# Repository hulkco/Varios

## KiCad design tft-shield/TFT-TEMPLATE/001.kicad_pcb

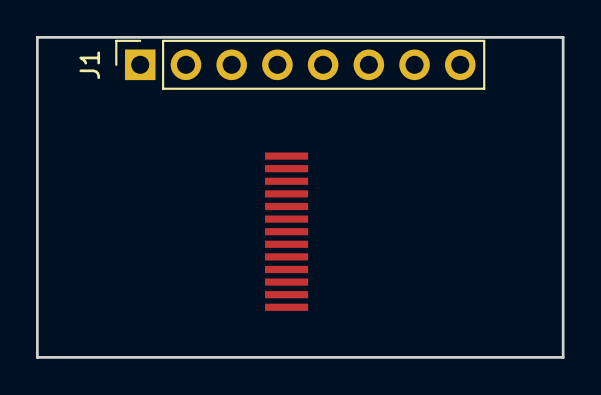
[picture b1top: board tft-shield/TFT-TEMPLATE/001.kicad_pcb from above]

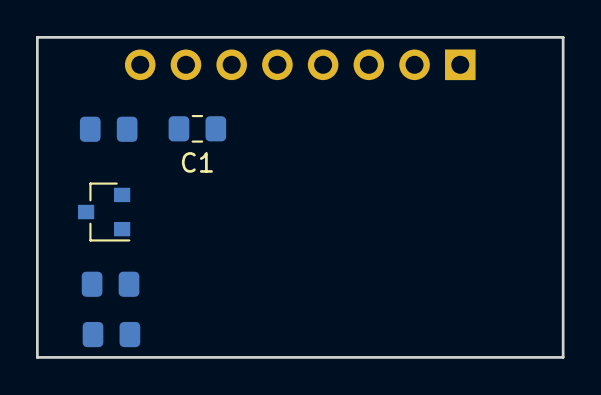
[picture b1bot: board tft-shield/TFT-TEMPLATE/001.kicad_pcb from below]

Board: 2 copper layers, 29.2 x 17.8 mm, 7 parts (5 on the bottom side), 12 nets, no tracks yet.

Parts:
C1: 1uF; C_0805_2012Metric_Pad1.15x1.40mm_HandSolder
J1: CONN_01X08; PinSocket_1x08_P2.54mm_Vertical
Q1: S8050; SOT-23
R1: 1k; R_0805_2012Metric_Pad1.15x1.40mm_HandSolder
R2: 10k; R_0805_2012Metric_Pad1.15x1.40mm_HandSolder
R3: 10ohm; R_0805_2012Metric_Pad1.15x1.40mm_HandSolder
U1: TFT_0.9680*160; TFT_0.96_SPI

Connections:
/BLK: J1.3, R1.2
/CS: J1.4, U1.7
/DC: J1.6, U1.5
/LEDK: R3.1, U1.11
/RES: J1.5, U1.6
/SCL: J1.7, U1.4
/SDA: J1.8, U1.3
GND: C1.2, J1.1, Q1.1, U1.8, U1.13
unnamed: C1.1, U1.10
unnamed: Q1.2, R1.1, R2.1
unnamed: Q1.3, R3.2
VCC: J1.2, R2.2, U1.12

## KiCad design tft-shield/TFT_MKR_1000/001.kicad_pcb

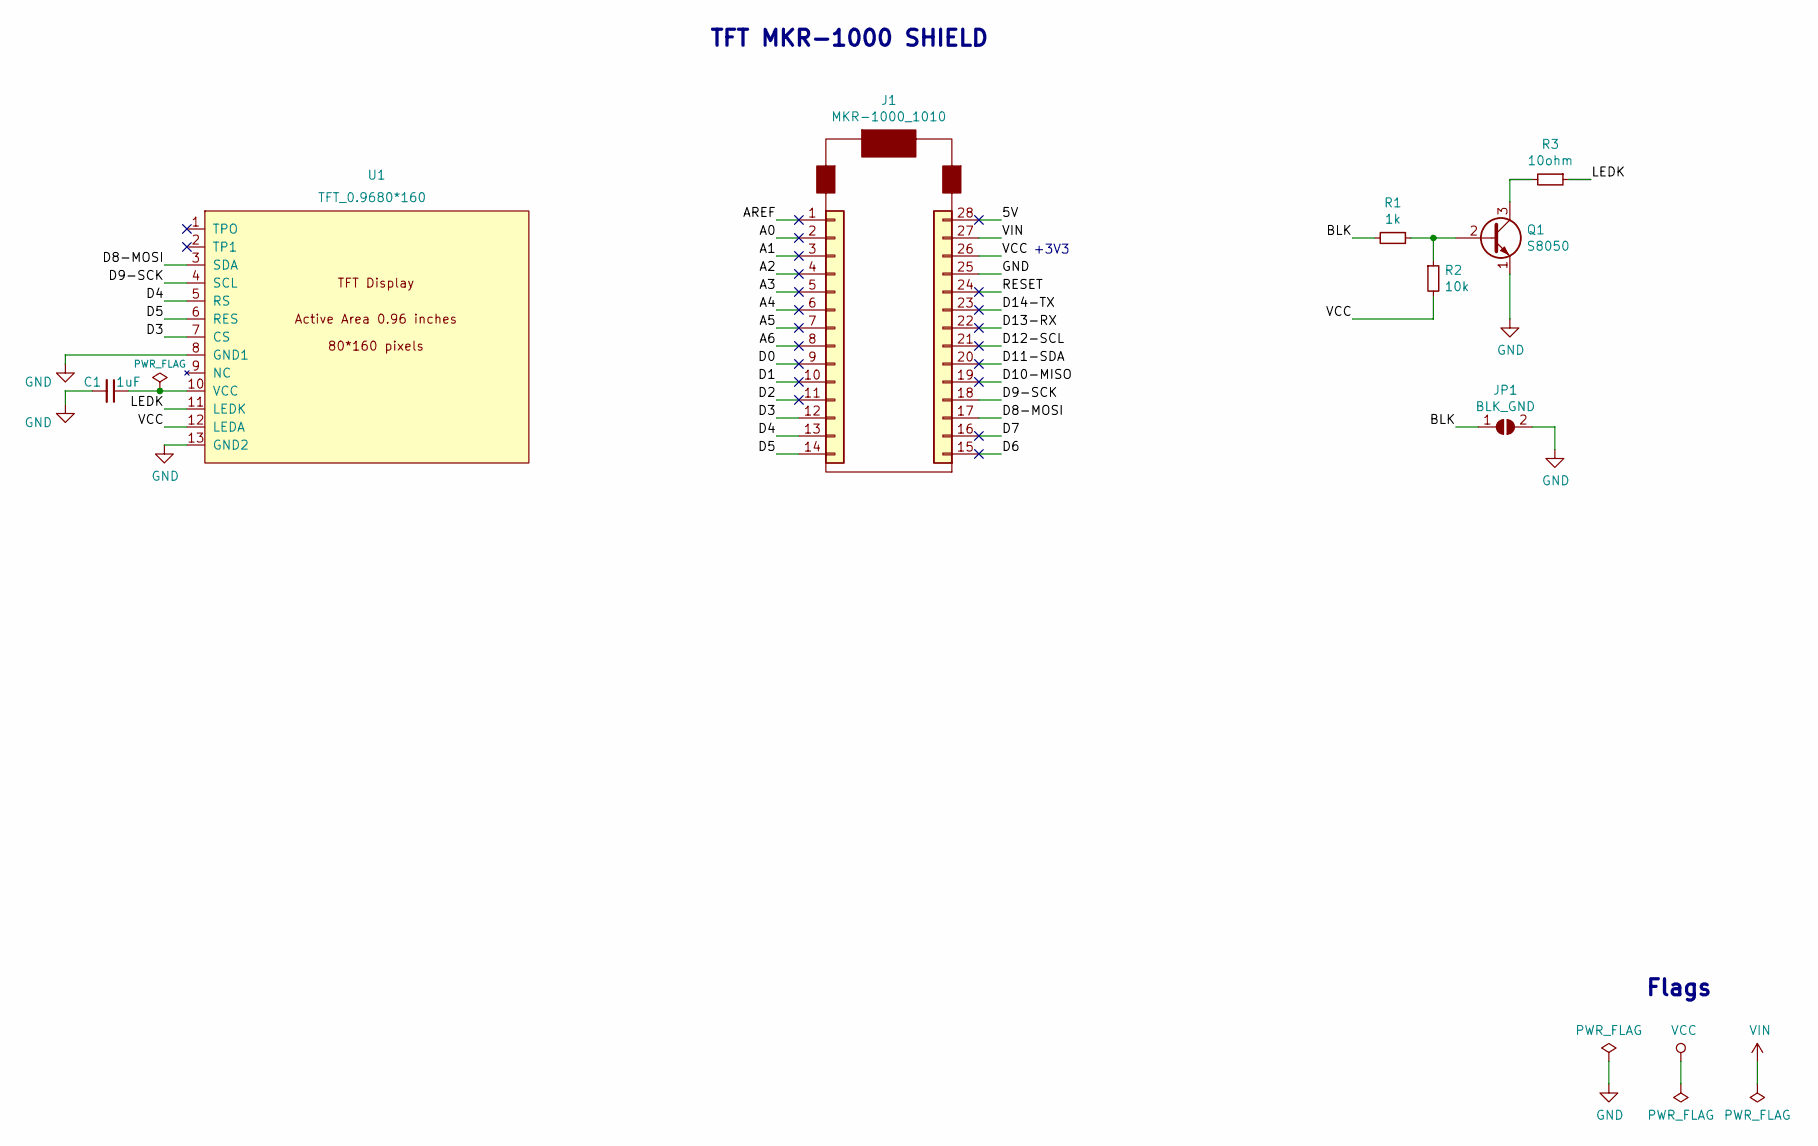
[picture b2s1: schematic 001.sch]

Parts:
C1: 1uF; C_0805_2012Metric_Pad1.15x1.40mm_HandSolder
J1: MKR-1000_1010; MKR-1000-1010
JP1: BLK_GND; SolderJumper-2_P1.3mm_Open_RoundedPad1.0x1.5mm
Q1: S8050; SOT-23
R1: 1k; R_0805_2012Metric_Pad1.15x1.40mm_HandSolder
R2: 10k; R_0805_2012Metric_Pad1.15x1.40mm_HandSolder
R3: 10ohm; R_0805_2012Metric_Pad1.15x1.40mm_HandSolder
U1: TFT_0.9680*160; TFT_0.96_SPI

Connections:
/5V: J1.28
/A0: J1.2
/A1: J1.3
/A2: J1.4
/A3: J1.5
/A4: J1.6
/A5: J1.7
/A6: J1.8
/AREF: J1.1
/BLK: JP1.1 (A), R1.2
/D0: J1.9
/D1: J1.10
/D2: J1.11
/D3: J1.12, U1.7 (CS)
/D4: J1.13, U1.5 (RS)
/D5: J1.14, U1.6 (RES)
/D6: J1.15
/D7: J1.16
/D8-MOSI: J1.17, U1.3 (SDA)
/D9-SCK: J1.18, U1.4 (SCL)
/D10-MISO: J1.19
/D11-SDA: J1.20
/D12-SCL: J1.21
/D13-RX: J1.22
/D14-TX: J1.23
/LEDK: R3.1, U1.11 (LEDK)
/RESET: J1.24
GND: C1.2, J1.25, JP1.2 (B), Q1.1 (E), U1.8 (GND1), U1.13 (GND2)
unnamed: C1.1, U1.10 (VCC)
unnamed: Q1.2 (B), R1.1, R2.1
unnamed: Q1.3 (C), R3.2
VCC: J1.26, R2.2, U1.12 (LEDA)
VIN: J1.27

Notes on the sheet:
TFT MKR-1000 SHIELD
Flags
+3V3

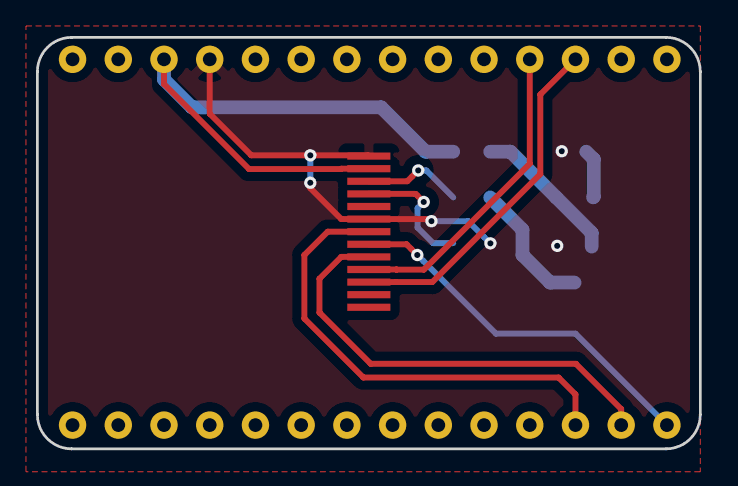
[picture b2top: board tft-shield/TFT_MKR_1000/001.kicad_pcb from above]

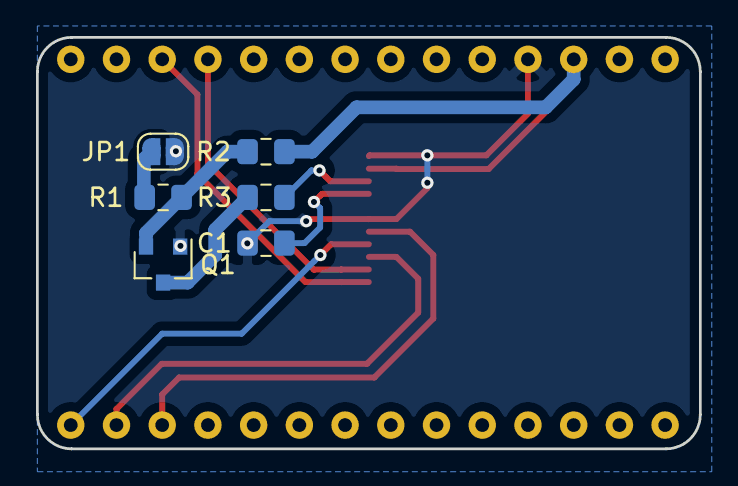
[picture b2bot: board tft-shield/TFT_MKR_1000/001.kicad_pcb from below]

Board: 2 copper layers, 36.8 x 22.9 mm, 8 parts (6 on the bottom side), 12 nets.

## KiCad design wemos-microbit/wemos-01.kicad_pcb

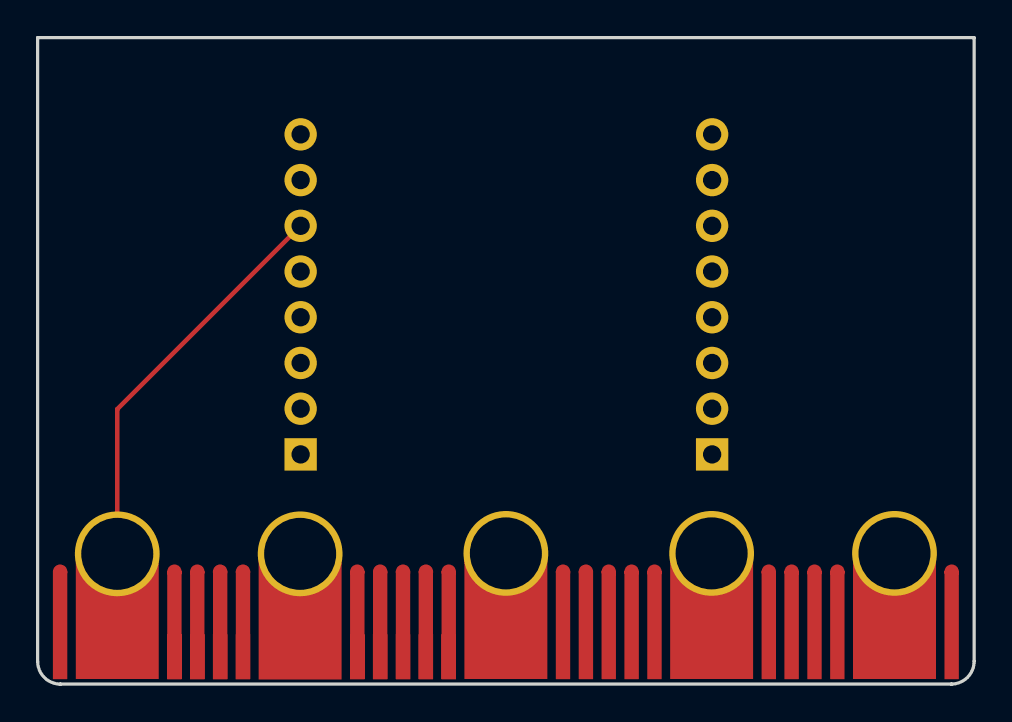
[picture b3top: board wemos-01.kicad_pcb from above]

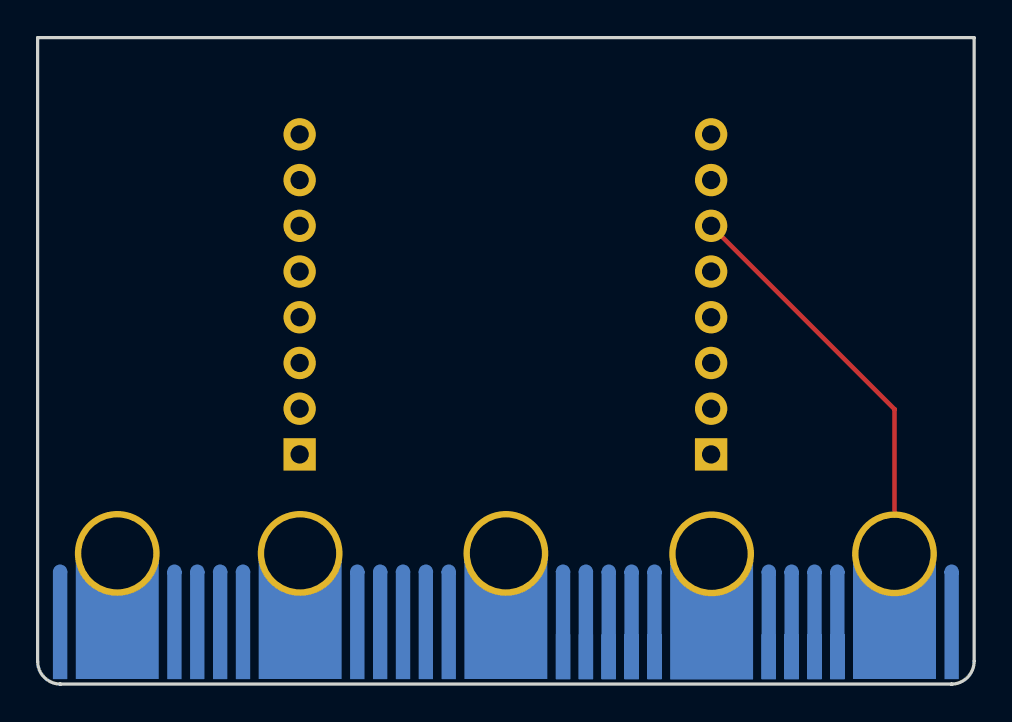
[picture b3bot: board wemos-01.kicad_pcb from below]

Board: 2 copper layers, 52.0 x 35.9 mm, 3 parts (2 on the bottom side), 9 nets.

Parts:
J1: Microbit_01X25; Microbit_PCB_Connector
P1, P2: CONN_01X08; D1_mini_Pin_Header

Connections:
/+3.3V: J1.18, J1.19, J1.20, P2.1
/A0: J1.13, P2.7
/D0: J1.2, P2.6
/D1: J1.21, P1.6
/D2: J1.22, P1.5
/D3: J1.7, P1.4
/D4: J1.11, P1.3
/GND: J1.23, J1.24, J1.25, P1.2
/RST: J1.9, P2.8

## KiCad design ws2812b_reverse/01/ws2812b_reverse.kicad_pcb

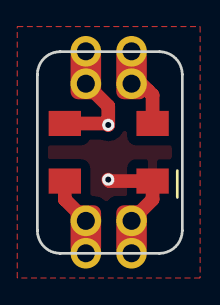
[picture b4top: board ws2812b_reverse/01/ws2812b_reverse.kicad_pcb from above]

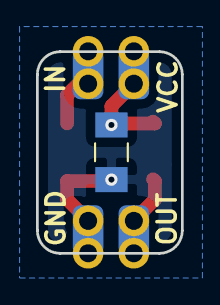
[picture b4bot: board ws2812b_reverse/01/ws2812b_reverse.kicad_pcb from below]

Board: 2 copper layers, 8.1 x 11.2 mm, 4 parts (2 on the bottom side), 4 nets.

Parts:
C1: 0.1uF; C_1206_3216Metric_Pad1.39x1.80mm_HandSolder
J1, J2: CONN_01X02; Pin_half-02x02_P2.54mm
LED1: LED-RGB-WS2812B-4SMD; LED-RGB-5050-SMD

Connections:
GND: C1.2, J2.2, LED1.1
unnamed: J1.2, LED1.2
unnamed: J2.1, LED1.4
VCC: C1.1, J1.1, LED1.3

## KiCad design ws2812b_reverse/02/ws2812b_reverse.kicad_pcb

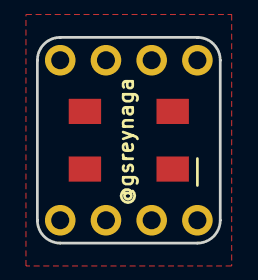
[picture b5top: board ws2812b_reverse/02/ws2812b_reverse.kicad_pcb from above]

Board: 2 copper layers, 10.2 x 11.4 mm, 4 parts (1 on the bottom side), 4 nets.

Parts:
C1: C; C_1206_3216Metric_Pad1.39x1.80mm_HandSolder
J1, J2: CONN_01X04; PinSocket_1x04_P2.54mm_WeMos
LED1: LED-RGB-WS2812B-4SMD; LED-RGB-5050-SMD

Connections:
GND: C1.2, J2.3, J2.4, LED1.1
unnamed: J1.3, J1.4, LED1.2
unnamed: J2.1, J2.2, LED1.4
VCC: C1.1, J1.1, J1.2, LED1.3
